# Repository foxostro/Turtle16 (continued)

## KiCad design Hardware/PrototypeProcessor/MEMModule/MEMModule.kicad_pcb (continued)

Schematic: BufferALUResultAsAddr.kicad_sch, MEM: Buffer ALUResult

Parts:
C6: 0.1μF; C_0603_1608Metric_Pad1.08x0.95mm_HandSolder
U5: 74AHCT16245; TSSOP-48_6.1x12.5mm_P0.5mm

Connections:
/MEM Prototype Inputs/Y_MEM0: U5.2 (1B1); also elsewhere on the board
/MEM Prototype Inputs/Y_MEM1: U5.3 (1B2); also elsewhere on the board
/MEM Prototype Inputs/Y_MEM2: U5.5 (1B3); also elsewhere on the board
/MEM Prototype Inputs/Y_MEM3: U5.6 (1B4); also elsewhere on the board
/MEM Prototype Inputs/Y_MEM4: U5.8 (1B5); also elsewhere on the board
/MEM Prototype Inputs/Y_MEM5: U5.9 (1B6); also elsewhere on the board
/MEM Prototype Inputs/Y_MEM6: U5.11 (1B7); also elsewhere on the board
/MEM Prototype Inputs/Y_MEM7: U5.12 (1B8); also elsewhere on the board
/MEM Prototype Inputs/Y_MEM8: U5.13 (2B1); also elsewhere on the board
/MEM Prototype Inputs/Y_MEM9: U5.14 (2B2); also elsewhere on the board
/MEM Prototype Inputs/Y_MEM10: U5.16 (2B3); also elsewhere on the board
/MEM Prototype Inputs/Y_MEM11: U5.17 (2B4); also elsewhere on the board
/MEM Prototype Inputs/Y_MEM12: U5.19 (2B5); also elsewhere on the board
/MEM Prototype Inputs/Y_MEM13: U5.20 (2B6); also elsewhere on the board
/MEM Prototype Inputs/Y_MEM14: U5.22 (2B7); also elsewhere on the board
/MEM Prototype Inputs/Y_MEM15: U5.23 (2B8); also elsewhere on the board
/MEM/~RDY: U5.25 (2~OE), U5.48 (1~OE); also elsewhere on the board
/Memory/Addr0: U5.47 (1A1); also elsewhere on the board
/Memory/Addr1: U5.46 (1A2); also elsewhere on the board
/Memory/Addr2: U5.44 (1A3); also elsewhere on the board
/Memory/Addr3: U5.43 (1A4); also elsewhere on the board
/Memory/Addr4: U5.41 (1A5); also elsewhere on the board
/Memory/Addr5: U5.40 (1A6); also elsewhere on the board
/Memory/Addr6: U5.38 (1A7); also elsewhere on the board
/Memory/Addr7: U5.37 (1A8); also elsewhere on the board
/Memory/Addr8: U5.36 (2A1); also elsewhere on the board
/Memory/Addr9: U5.35 (2A2); also elsewhere on the board
/Memory/Addr10: U5.33 (2A3); also elsewhere on the board
/Memory/Addr11: U5.32 (2A4); also elsewhere on the board
/Memory/Addr12: U5.30 (2A5); also elsewhere on the board
/Memory/Addr13: U5.29 (2A6); also elsewhere on the board
/Memory/Addr14: U5.27 (2A7); also elsewhere on the board
/Memory/Addr15: U5.26 (2A8); also elsewhere on the board
GND: C6.2, U5.1 (1DIR), U5.4 (GND), U5.10 (GND), U5.15 (GND), U5.21 (GND), U5.24 (2DIR), U5.28 (GND), U5.34 (GND), U5.39 (GND), U5.45 (GND); also elsewhere on the board
VCC: C6.1, U5.7 (VCC), U5.18 (VCC), U5.31 (VCC), U5.42 (VCC); also elsewhere on the board

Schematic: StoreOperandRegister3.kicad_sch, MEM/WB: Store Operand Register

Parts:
C8: 0.1μF; C_0603_1608Metric_Pad1.08x0.95mm_HandSolder
U7: 74ABT16374; TSSOP-48_6.1x12.5mm_P0.5mm

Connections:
/MEM Prototype Inputs/Phi1b: U7.25 (2CLK), U7.48 (1CLK); also elsewhere on the board
/MEM Prototype Outputs/StoreOp_WB0: U7.2 (1Q1); also elsewhere on the board
/MEM Prototype Outputs/StoreOp_WB1: U7.3 (1Q2); also elsewhere on the board
/MEM Prototype Outputs/StoreOp_WB2: U7.5 (1Q3); also elsewhere on the board
/MEM Prototype Outputs/StoreOp_WB3: U7.6 (1Q4); also elsewhere on the board
/MEM Prototype Outputs/StoreOp_WB4: U7.8 (1Q5); also elsewhere on the board
/MEM Prototype Outputs/StoreOp_WB5: U7.9 (1Q6); also elsewhere on the board
/MEM Prototype Outputs/StoreOp_WB6: U7.11 (1Q7); also elsewhere on the board
/MEM Prototype Outputs/StoreOp_WB7: U7.12 (1Q8); also elsewhere on the board
/MEM Prototype Outputs/StoreOp_WB8: U7.13 (2Q1); also elsewhere on the board
/MEM Prototype Outputs/StoreOp_WB9: U7.14 (2Q2); also elsewhere on the board
/MEM Prototype Outputs/StoreOp_WB10: U7.16 (2Q3); also elsewhere on the board
/MEM Prototype Outputs/StoreOp_WB11: U7.17 (2Q4); also elsewhere on the board
/MEM Prototype Outputs/StoreOp_WB12: U7.19 (2Q5); also elsewhere on the board
/MEM Prototype Outputs/StoreOp_WB13: U7.20 (2Q6); also elsewhere on the board
/MEM Prototype Outputs/StoreOp_WB14: U7.22 (2Q7); also elsewhere on the board
/MEM Prototype Outputs/StoreOp_WB15: U7.23 (2Q8); also elsewhere on the board
/Memory/IO0: U7.47 (1D1); also elsewhere on the board
/Memory/IO1: U7.46 (1D2); also elsewhere on the board
/Memory/IO2: U7.44 (1D3); also elsewhere on the board
/Memory/IO3: U7.43 (1D4); also elsewhere on the board
/Memory/IO4: U7.41 (1D5); also elsewhere on the board
/Memory/IO5: U7.40 (1D6); also elsewhere on the board
/Memory/IO6: U7.38 (1D7); also elsewhere on the board
/Memory/IO7: U7.37 (1D8); also elsewhere on the board
/Memory/IO8: U7.36 (2D1); also elsewhere on the board
/Memory/IO9: U7.35 (2D2); also elsewhere on the board
/Memory/IO10: U7.33 (2D3); also elsewhere on the board
/Memory/IO11: U7.32 (2D4); also elsewhere on the board
/Memory/IO12: U7.30 (2D5); also elsewhere on the board
/Memory/IO13: U7.29 (2D6); also elsewhere on the board
/Memory/IO14: U7.27 (2D7); also elsewhere on the board
/Memory/IO15: U7.26 (2D8); also elsewhere on the board
GND: C8.2, U7.1 (1~OE), U7.4 (GND), U7.10 (GND), U7.15 (GND), U7.21 (GND), U7.24 (2~OE), U7.28 (GND), U7.34 (GND), U7.39 (GND), U7.45 (GND); also elsewhere on the board
VCC: C8.1, U7.7 (VCC), U7.18 (VCC), U7.31 (VCC), U7.42 (VCC); also elsewhere on the board

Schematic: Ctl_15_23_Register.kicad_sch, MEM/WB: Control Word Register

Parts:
C7: 0.1μF; C_0603_1608Metric_Pad1.08x0.95mm_HandSolder
U6: 74ABT574; TSSOP-20_4.4x6.5mm_P0.65mm

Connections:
/MEM Prototype Inputs/Ctl_MEM17: U6.9 (D7); also elsewhere on the board
/MEM Prototype Inputs/Ctl_MEM18: U6.8 (D6); also elsewhere on the board
/MEM Prototype Inputs/Ctl_MEM19: U6.7 (D5); also elsewhere on the board
/MEM Prototype Inputs/Ctl_MEM20: U6.6 (D4); also elsewhere on the board
/MEM Prototype Inputs/Phi1b: U6.11 (Cp); also elsewhere on the board
/MEM Prototype Inputs/SelC_MEM0: U6.5 (D3); also elsewhere on the board
/MEM Prototype Inputs/SelC_MEM1: U6.4 (D2); also elsewhere on the board
/MEM Prototype Inputs/SelC_MEM2: U6.3 (D1); also elsewhere on the board
/MEM Prototype Outputs/Ctl_WB17: U6.12 (Q7); also elsewhere on the board
/MEM Prototype Outputs/Ctl_WB18: U6.13 (Q6); also elsewhere on the board
/MEM Prototype Outputs/Ctl_WB19: U6.14 (Q5); also elsewhere on the board
/MEM Prototype Outputs/Ctl_WB20: U6.15 (Q4); also elsewhere on the board
/MEM Prototype Outputs/SelC_WB0: U6.16 (Q3); also elsewhere on the board
/MEM Prototype Outputs/SelC_WB1: U6.17 (Q2); also elsewhere on the board
/MEM Prototype Outputs/SelC_WB2: U6.18 (Q1); also elsewhere on the board
GND: C7.2, U6.1 (OE), U6.10 (GND); also elsewhere on the board
VCC: C7.1, U6.2 (D0), U6.20 (VCC); also elsewhere on the board

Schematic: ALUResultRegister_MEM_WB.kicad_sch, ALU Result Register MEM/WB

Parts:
C11: 0.1μF; C_0603_1608Metric_Pad1.08x0.95mm_HandSolder
U8: 74ABT16374; TSSOP-48_6.1x12.5mm_P0.5mm

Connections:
/MEM Prototype Inputs/Phi1b: U8.25 (2CLK), U8.48 (1CLK); also elsewhere on the board
/MEM Prototype Inputs/Y_MEM0: U8.47 (1D1); also elsewhere on the board
/MEM Prototype Inputs/Y_MEM1: U8.46 (1D2); also elsewhere on the board
/MEM Prototype Inputs/Y_MEM2: U8.44 (1D3); also elsewhere on the board
/MEM Prototype Inputs/Y_MEM3: U8.43 (1D4); also elsewhere on the board
/MEM Prototype Inputs/Y_MEM4: U8.41 (1D5); also elsewhere on the board
/MEM Prototype Inputs/Y_MEM5: U8.40 (1D6); also elsewhere on the board
/MEM Prototype Inputs/Y_MEM6: U8.38 (1D7); also elsewhere on the board
/MEM Prototype Inputs/Y_MEM7: U8.37 (1D8); also elsewhere on the board
/MEM Prototype Inputs/Y_MEM8: U8.36 (2D1); also elsewhere on the board
/MEM Prototype Inputs/Y_MEM9: U8.35 (2D2); also elsewhere on the board
/MEM Prototype Inputs/Y_MEM10: U8.33 (2D3); also elsewhere on the board
/MEM Prototype Inputs/Y_MEM11: U8.32 (2D4); also elsewhere on the board
/MEM Prototype Inputs/Y_MEM12: U8.30 (2D5); also elsewhere on the board
/MEM Prototype Inputs/Y_MEM13: U8.29 (2D6); also elsewhere on the board
/MEM Prototype Inputs/Y_MEM14: U8.27 (2D7); also elsewhere on the board
/MEM Prototype Inputs/Y_MEM15: U8.26 (2D8); also elsewhere on the board
/MEM Prototype Outputs/Y_WB0: U8.2 (1Q1); also elsewhere on the board
/MEM Prototype Outputs/Y_WB1: U8.3 (1Q2); also elsewhere on the board
/MEM Prototype Outputs/Y_WB2: U8.5 (1Q3); also elsewhere on the board
/MEM Prototype Outputs/Y_WB3: U8.6 (1Q4); also elsewhere on the board
/MEM Prototype Outputs/Y_WB4: U8.8 (1Q5); also elsewhere on the board
/MEM Prototype Outputs/Y_WB5: U8.9 (1Q6); also elsewhere on the board
/MEM Prototype Outputs/Y_WB6: U8.11 (1Q7); also elsewhere on the board
/MEM Prototype Outputs/Y_WB7: U8.12 (1Q8); also elsewhere on the board
/MEM Prototype Outputs/Y_WB8: U8.13 (2Q1); also elsewhere on the board
/MEM Prototype Outputs/Y_WB9: U8.14 (2Q2); also elsewhere on the board
/MEM Prototype Outputs/Y_WB10: U8.16 (2Q3); also elsewhere on the board
/MEM Prototype Outputs/Y_WB11: U8.17 (2Q4); also elsewhere on the board
/MEM Prototype Outputs/Y_WB12: U8.19 (2Q5); also elsewhere on the board
/MEM Prototype Outputs/Y_WB13: U8.20 (2Q6); also elsewhere on the board
/MEM Prototype Outputs/Y_WB14: U8.22 (2Q7); also elsewhere on the board
/MEM Prototype Outputs/Y_WB15: U8.23 (2Q8); also elsewhere on the board
GND: C11.2, U8.1 (1~OE), U8.4 (GND), U8.10 (GND), U8.15 (GND), U8.21 (GND), U8.24 (2~OE), U8.28 (GND), U8.34 (GND), U8.39 (GND), U8.45 (GND); also elsewhere on the board
VCC: C11.1, U8.7 (VCC), U8.18 (VCC), U8.31 (VCC), U8.42 (VCC); also elsewhere on the board

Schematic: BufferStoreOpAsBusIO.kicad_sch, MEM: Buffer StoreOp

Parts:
C5: 0.1μF; C_0603_1608Metric_Pad1.08x0.95mm_HandSolder
TP41: ~{Assert}; TestPoint_Pad_D1.0mm
U4: 74AHCT16245; TSSOP-48_6.1x12.5mm_P0.5mm

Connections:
/MEM Prototype Inputs/StoreOp_MEM0: U4.23 (2B8); also elsewhere on the board
/MEM Prototype Inputs/StoreOp_MEM1: U4.22 (2B7); also elsewhere on the board
/MEM Prototype Inputs/StoreOp_MEM2: U4.20 (2B6); also elsewhere on the board
/MEM Prototype Inputs/StoreOp_MEM3: U4.19 (2B5); also elsewhere on the board
/MEM Prototype Inputs/StoreOp_MEM4: U4.17 (2B4); also elsewhere on the board
/MEM Prototype Inputs/StoreOp_MEM5: U4.16 (2B3); also elsewhere on the board
/MEM Prototype Inputs/StoreOp_MEM6: U4.14 (2B2); also elsewhere on the board
/MEM Prototype Inputs/StoreOp_MEM7: U4.13 (2B1); also elsewhere on the board
/MEM Prototype Inputs/StoreOp_MEM8: U4.12 (1B8); also elsewhere on the board
/MEM Prototype Inputs/StoreOp_MEM9: U4.11 (1B7); also elsewhere on the board
/MEM Prototype Inputs/StoreOp_MEM10: U4.9 (1B6); also elsewhere on the board
/MEM Prototype Inputs/StoreOp_MEM11: U4.8 (1B5); also elsewhere on the board
/MEM Prototype Inputs/StoreOp_MEM12: U4.6 (1B4); also elsewhere on the board
/MEM Prototype Inputs/StoreOp_MEM13: U4.5 (1B3); also elsewhere on the board
/MEM Prototype Inputs/StoreOp_MEM14: U4.3 (1B2); also elsewhere on the board
/MEM Prototype Inputs/StoreOp_MEM15: U4.2 (1B1); also elsewhere on the board
/MEM/Buffer StoreOp As Bus I/O/~Assert: TP41.1, U4.25 (2~OE), U4.48 (1~OE); also elsewhere on the board
/Memory/IO0: U4.26 (2A8); also elsewhere on the board
/Memory/IO1: U4.27 (2A7); also elsewhere on the board
/Memory/IO2: U4.29 (2A6); also elsewhere on the board
/Memory/IO3: U4.30 (2A5); also elsewhere on the board
/Memory/IO4: U4.32 (2A4); also elsewhere on the board
/Memory/IO5: U4.33 (2A3); also elsewhere on the board
/Memory/IO6: U4.35 (2A2); also elsewhere on the board
/Memory/IO7: U4.36 (2A1); also elsewhere on the board
/Memory/IO8: U4.37 (1A8); also elsewhere on the board
/Memory/IO9: U4.38 (1A7); also elsewhere on the board
/Memory/IO10: U4.40 (1A6); also elsewhere on the board
/Memory/IO11: U4.41 (1A5); also elsewhere on the board
/Memory/IO12: U4.43 (1A4); also elsewhere on the board
/Memory/IO13: U4.44 (1A3); also elsewhere on the board
/Memory/IO14: U4.46 (1A2); also elsewhere on the board
/Memory/IO15: U4.47 (1A1); also elsewhere on the board
GND: C5.2, U4.1 (1DIR), U4.4 (GND), U4.10 (GND), U4.15 (GND), U4.21 (GND), U4.24 (2DIR), U4.28 (GND), U4.34 (GND), U4.39 (GND), U4.45 (GND); also elsewhere on the board
VCC: C5.1, U4.7 (VCC), U4.18 (VCC), U4.31 (VCC), U4.42 (VCC); also elsewhere on the board

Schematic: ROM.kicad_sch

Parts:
C14, C15: 0.1μF; C_0603_1608Metric_Pad1.08x0.95mm_HandSolder
U11, U12: SST39SF010; 843221B1RKTP

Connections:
/MEM Prototype Inputs/FLUSH_IF: U11.22 (CE), U12.22 (CE); also elsewhere on the board
/Memory/Ins_IF0: U11.13 (D0); also elsewhere on the board
/Memory/Ins_IF1: U11.14 (D1); also elsewhere on the board
/Memory/Ins_IF2: U11.15 (D2); also elsewhere on the board
/Memory/Ins_IF3: U11.17 (D3); also elsewhere on the board
/Memory/Ins_IF4: U11.18 (D4); also elsewhere on the board
/Memory/Ins_IF5: U11.19 (D5); also elsewhere on the board
/Memory/Ins_IF6: U11.20 (D6); also elsewhere on the board
/Memory/Ins_IF7: U11.21 (D7); also elsewhere on the board
/Memory/Ins_IF8: U12.13 (D0); also elsewhere on the board
/Memory/Ins_IF9: U12.14 (D1); also elsewhere on the board
/Memory/Ins_IF10: U12.15 (D2); also elsewhere on the board
/Memory/Ins_IF11: U12.17 (D3); also elsewhere on the board
/Memory/Ins_IF12: U12.18 (D4); also elsewhere on the board
/Memory/Ins_IF13: U12.19 (D5); also elsewhere on the board
/Memory/Ins_IF14: U12.20 (D6); also elsewhere on the board
/Memory/Ins_IF15: U12.21 (D7); also elsewhere on the board
/Memory/PC0: U11.12 (A0), U12.12 (A0); also elsewhere on the board
/Memory/PC1: U11.11 (A1), U12.11 (A1); also elsewhere on the board
/Memory/PC2: U11.10 (A2), U12.10 (A2); also elsewhere on the board
/Memory/PC3: U11.9 (A3), U12.9 (A3); also elsewhere on the board
/Memory/PC4: U11.8 (A4), U12.8 (A4); also elsewhere on the board
/Memory/PC5: U11.7 (A5), U12.7 (A5); also elsewhere on the board
/Memory/PC6: U11.6 (A6), U12.6 (A6); also elsewhere on the board
/Memory/PC7: U11.5 (A7), U12.5 (A7); also elsewhere on the board
/Memory/PC8: U11.27 (A8), U12.27 (A8); also elsewhere on the board
/Memory/PC9: U11.26 (A9), U12.26 (A9); also elsewhere on the board
/Memory/PC10: U11.23 (A10), U12.23 (A10); also elsewhere on the board
/Memory/PC11: U11.25 (A11), U12.25 (A11); also elsewhere on the board
/Memory/PC12: U11.4 (A12), U12.4 (A12); also elsewhere on the board
/Memory/PC13: U11.28 (A13), U12.28 (A13); also elsewhere on the board
/Memory/PC14: U11.29 (A14), U12.29 (A14); also elsewhere on the board
/Memory/PC15: U11.3 (A15), U12.3 (A15); also elsewhere on the board
/Memory/RAMEN_R: U11.24 (OE), U12.24 (OE); also elsewhere on the board
GND: C14.2, C15.2, U11.2 (A16), U11.16 (GND), U12.2 (A16), U12.16 (GND); also elsewhere on the board
VCC: C14.1, C15.1, U11.31 (PGM), U11.32 (VCC), U12.31 (PGM), U12.32 (VCC); also elsewhere on the board

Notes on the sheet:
RAMEN_R enables the ROM. The right side of the RAM is used for Instruction Fetch. If the IF stage is not being fed by RAM then it is being fed by this ROM.

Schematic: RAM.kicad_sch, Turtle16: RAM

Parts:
C9, C10: 0.1μF; C_0603_1608Metric_Pad1.08x0.95mm_HandSolder
IC1: 7028L20PFGI; TQFP-100_14x14mm_P0.5mm; Manufacturer_Part_Number 7028L20PFGI; Mouser Part Number 972-7028L20PFGI

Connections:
/MEM Prototype Inputs/FLUSH_IF: IC1.59 (~OER); also elsewhere on the board
/Memory/Addr0: IC1.92 (A0L); also elsewhere on the board
/Memory/Addr1: IC1.93 (A1L); also elsewhere on the board
/Memory/Addr2: IC1.94 (A2L); also elsewhere on the board
/Memory/Addr3: IC1.95 (A3L); also elsewhere on the board
/Memory/Addr4: IC1.96 (A4L); also elsewhere on the board
/Memory/Addr5: IC1.97 (A5L); also elsewhere on the board
/Memory/Addr6: IC1.98 (A6L); also elsewhere on the board
/Memory/Addr7: IC1.99 (A7L); also elsewhere on the board
/Memory/Addr8: IC1.100 (A8L); also elsewhere on the board
/Memory/Addr9: IC1.1 (A9L); also elsewhere on the board
/Memory/Addr10: IC1.2 (A10L); also elsewhere on the board
/Memory/Addr11: IC1.3 (A11L); also elsewhere on the board
/Memory/Addr12: IC1.4 (A12L); also elsewhere on the board
/Memory/Addr13: IC1.5 (A13L); also elsewhere on the board
/Memory/Addr14: IC1.6 (A14L); also elsewhere on the board
/Memory/Addr15: IC1.7 (A15L); also elsewhere on the board
/Memory/IO0: IC1.37 (I/O0L); also elsewhere on the board
/Memory/IO1: IC1.36 (I/O1L); also elsewhere on the board
/Memory/IO2: IC1.34 (I/O2L); also elsewhere on the board
/Memory/IO3: IC1.33 (I/O3L); also elsewhere on the board
/Memory/IO4: IC1.32 (I/O4L); also elsewhere on the board
/Memory/IO5: IC1.31 (I/O5L); also elsewhere on the board
/Memory/IO6: IC1.30 (I/O6L); also elsewhere on the board
/Memory/IO7: IC1.29 (I/O7L); also elsewhere on the board
/Memory/IO8: IC1.27 (I/O8L); also elsewhere on the board
/Memory/IO9: IC1.26 (I/O9L); also elsewhere on the board
/Memory/IO10: IC1.25 (I/O10L); also elsewhere on the board
/Memory/IO11: IC1.24 (I/O11L); also elsewhere on the board
/Memory/IO12: IC1.23 (I/O12L); also elsewhere on the board
/Memory/IO13: IC1.22 (I/O13L); also elsewhere on the board
/Memory/IO14: IC1.21 (I/O14L); also elsewhere on the board
/Memory/IO15: IC1.20 (I/O15L); also elsewhere on the board
/Memory/Ins_IF0: IC1.39 (I/O0R); also elsewhere on the board
/Memory/Ins_IF1: IC1.40 (I/O1R); also elsewhere on the board
/Memory/Ins_IF2: IC1.41 (I/O2R); also elsewhere on the board
/Memory/Ins_IF3: IC1.42 (I/O3R); also elsewhere on the board
/Memory/Ins_IF4: IC1.43 (I/O4R); also elsewhere on the board
/Memory/Ins_IF5: IC1.44 (I/O5R); also elsewhere on the board
/Memory/Ins_IF6: IC1.45 (I/O6R); also elsewhere on the board
/Memory/Ins_IF7: IC1.47 (I/O7R); also elsewhere on the board
/Memory/Ins_IF8: IC1.48 (I/O8R); also elsewhere on the board
/Memory/Ins_IF9: IC1.49 (I/O9R); also elsewhere on the board
/Memory/Ins_IF10: IC1.51 (I/O10R); also elsewhere on the board
/Memory/Ins_IF11: IC1.52 (I/O11R); also elsewhere on the board
/Memory/Ins_IF12: IC1.53 (I/O12R); also elsewhere on the board
/Memory/Ins_IF13: IC1.54 (I/O13R); also elsewhere on the board
/Memory/Ins_IF14: IC1.55 (I/O14R); also elsewhere on the board
/Memory/Ins_IF15: IC1.56 (I/O15R); also elsewhere on the board
/Memory/PC0: IC1.84 (A0R); also elsewhere on the board
/Memory/PC1: IC1.83 (A1R); also elsewhere on the board
/Memory/PC2: IC1.82 (A2R); also elsewhere on the board
/Memory/PC3: IC1.81 (A3R); also elsewhere on the board
/Memory/PC4: IC1.80 (A4R); also elsewhere on the board
/Memory/PC5: IC1.79 (A5R); also elsewhere on the board
/Memory/PC6: IC1.78 (A6R); also elsewhere on the board
/Memory/PC7: IC1.77 (A7R); also elsewhere on the board
/Memory/PC8: IC1.76 (A8R); also elsewhere on the board
/Memory/PC9: IC1.75 (A9R); also elsewhere on the board
/Memory/PC10: IC1.74 (A10R); also elsewhere on the board
/Memory/PC11: IC1.73 (A11R); also elsewhere on the board
/Memory/PC12: IC1.72 (A12R); also elsewhere on the board
/Memory/PC13: IC1.71 (A13R); also elsewhere on the board
/Memory/PC14: IC1.70 (A14R); also elsewhere on the board
/Memory/PC15: IC1.69 (A15R); also elsewhere on the board
/Memory/RAMEN_L: IC1.13 (CE1L); also elsewhere on the board
/Memory/RAMEN_R: IC1.63 (CE1R); also elsewhere on the board
/Memory/~RAMEN_L: IC1.12 (~CE0L); also elsewhere on the board
/Memory/~RAMEN_R: IC1.64 (~CE0R); also elsewhere on the board
/System Bus Connector/~MemLoad: IC1.17 (~OEL); also elsewhere on the board
/System Bus Connector/~MemStore: IC1.16 (R/~WL); also elsewhere on the board
GND: C9.2, C10.2, IC1.10 (~LBL), IC1.11 (~UBL), IC1.18 (GND_1), IC1.19 (GND_2), IC1.35 (GND_3), IC1.38 (GND_4), IC1.57 (GND_5), IC1.58 (GND_6), IC1.61 (GND_7), IC1.65 (~UBR), IC1.66 (~LBR), IC1.87 (M/~S), IC1.88 (GND_8); also elsewhere on the board
VCC: C9.1, C10.1, IC1.14 (~SEML), IC1.15 (VCC_1), IC1.28 (VCC_2), IC1.46 (VCC_3), IC1.60 (R/~WR), IC1.62 (~SEMR), IC1.86 (~BUSYR), IC1.89 (~BUSYL); also elsewhere on the board

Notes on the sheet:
The RAM is configured in ~{S} mode to disable the onboard write arbitration logic.
If the IF stage is not being fed by ROM then it is being fed by RAM.

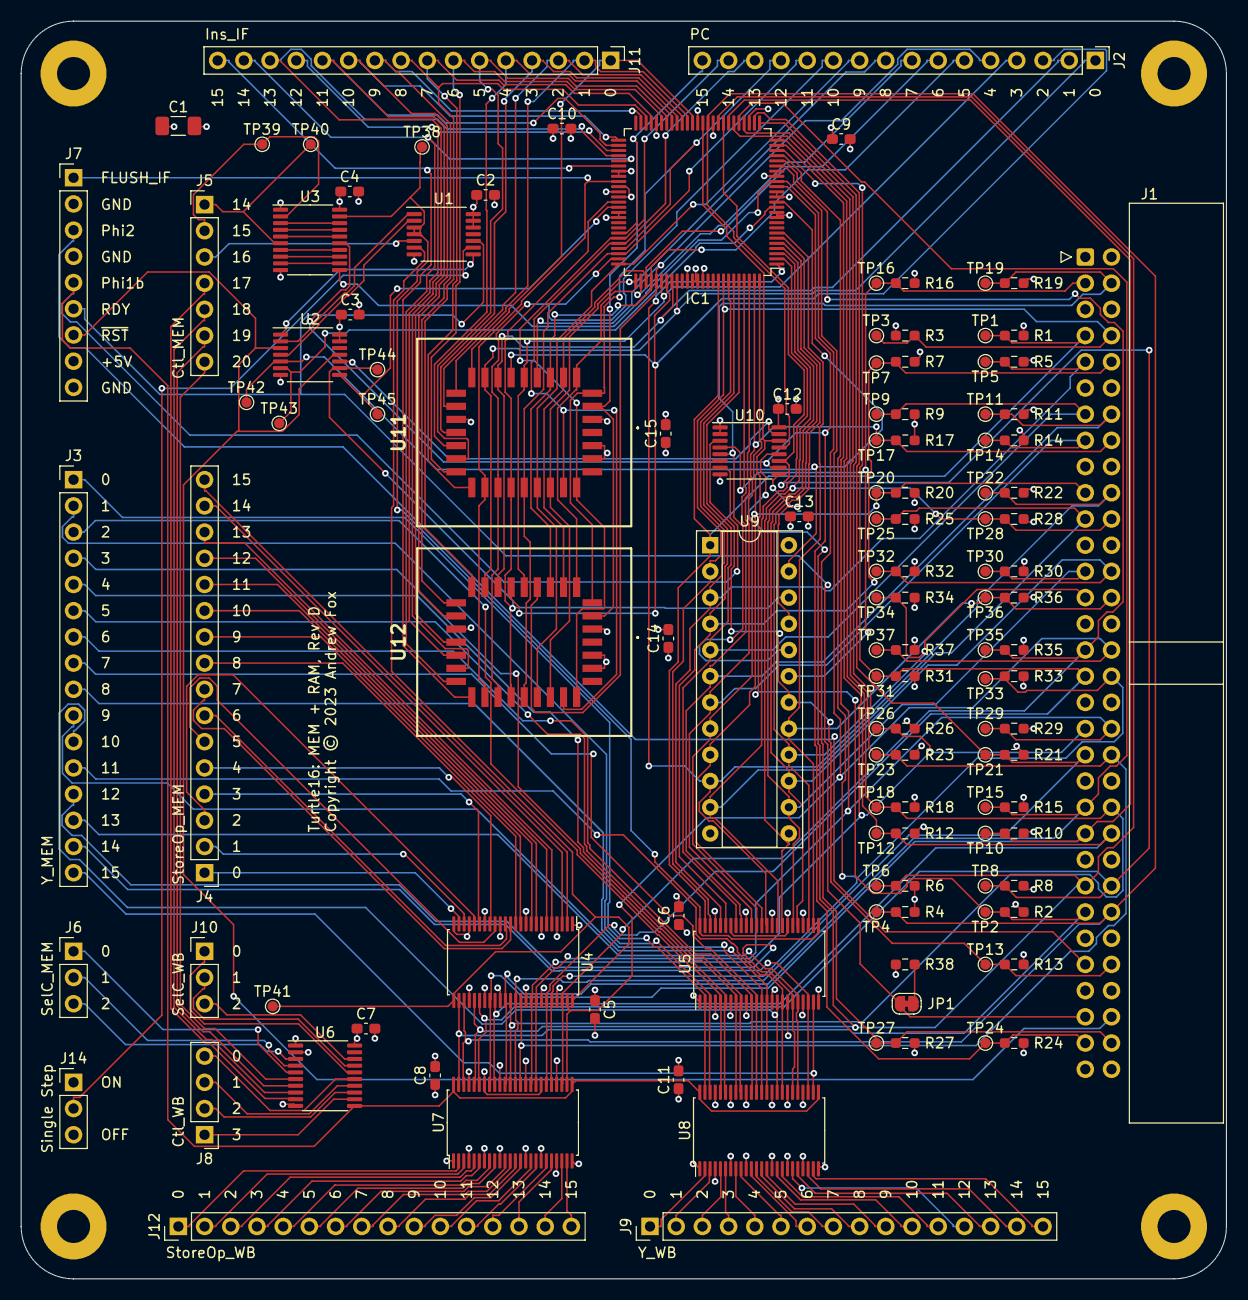
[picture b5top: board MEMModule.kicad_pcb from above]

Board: 4 copper layers, 116.8 x 121.9 mm, 129 parts (0 on the bottom side), 176 nets.

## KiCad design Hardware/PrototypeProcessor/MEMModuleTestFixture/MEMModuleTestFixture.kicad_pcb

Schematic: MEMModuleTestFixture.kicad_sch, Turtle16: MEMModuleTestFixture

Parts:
A1: Arduino_Nano_Every; Arduino_Nano
C1: 100µF; C_1206_3216Metric_Pad1.33x1.80mm_HandSolder
H1, H2, H3, H4: MountingHole_Pad; MountingHole_3.2mm_M3_Pad
J1: Power; 172448-0002

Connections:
/System Memory Bus Input/SCK: A1.24 (SCL/A5); also elsewhere on the board
/System Memory Bus Input/SO: A1.25 (A6); also elsewhere on the board
/System Memory Bus Input/~PL: A1.23 (SDA/A4); also elsewhere on the board
/System Memory Bus Output/RCLK: A1.21 (A2); also elsewhere on the board
/System Memory Bus Output/SCK: A1.20 (A1); also elsewhere on the board
/System Memory Bus Output/SI: A1.22 (A3); also elsewhere on the board
/System Memory Bus Output/~CLR: A1.19 (A0); also elsewhere on the board
/Test Fixture Inputs/SCK: A1.10 (D7); also elsewhere on the board
/Test Fixture Inputs/SO: A1.9 (D6); also elsewhere on the board
/Test Fixture Inputs/~PL: A1.11 (D8); also elsewhere on the board
/Test Fixture Outputs/RCLK: A1.6 (D3); also elsewhere on the board
/Test Fixture Outputs/SCK: A1.7 (D4); also elsewhere on the board
/Test Fixture Outputs/SI: A1.5 (D2); also elsewhere on the board
/Test Fixture Outputs/~CLR: A1.8 (D5); also elsewhere on the board
GND: A1.4 (GND), A1.29 (GND), C1.2, H1.1, H2.1, H3.1, H4.1, J1.2; also elsewhere on the board
VCC: A1.3 (~RESET), A1.28 (~RESET), A1.30 (VIN), C1.1, J1.1; also elsewhere on the board

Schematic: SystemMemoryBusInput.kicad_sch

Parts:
C26, C27, C28, C29, C30: 0.1µF; C_0603_1608Metric
U25, U26, U27, U28, U29: 74HC165; TSSOP-16_4.4x5mm_P0.65mm

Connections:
/System Bus Connector/Addr0: U27.11 (D0); also elsewhere on the board
/System Bus Connector/Addr1: U27.12 (D1); also elsewhere on the board
/System Bus Connector/Addr2: U27.13 (D2); also elsewhere on the board
/System Bus Connector/Addr3: U27.14 (D3); also elsewhere on the board
/System Bus Connector/Addr4: U27.3 (D4); also elsewhere on the board
/System Bus Connector/Addr5: U27.4 (D5); also elsewhere on the board
/System Bus Connector/Addr6: U27.5 (D6); also elsewhere on the board
/System Bus Connector/Addr7: U27.6 (D7); also elsewhere on the board
/System Bus Connector/Addr8: U28.11 (D0); also elsewhere on the board
/System Bus Connector/Addr9: U28.12 (D1); also elsewhere on the board
/System Bus Connector/Addr10: U28.13 (D2); also elsewhere on the board
/System Bus Connector/Addr11: U28.14 (D3); also elsewhere on the board
/System Bus Connector/Addr12: U28.3 (D4); also elsewhere on the board
/System Bus Connector/Addr13: U28.4 (D5); also elsewhere on the board
/System Bus Connector/Addr14: U28.5 (D6); also elsewhere on the board
/System Bus Connector/Addr15: U28.6 (D7); also elsewhere on the board
/System Bus Connector/Bank0: U29.11 (D0); also elsewhere on the board
/System Bus Connector/Bank1: U29.12 (D1); also elsewhere on the board
/System Bus Connector/Bank2: U29.13 (D2); also elsewhere on the board
/System Bus Connector/IO0: U25.11 (D0); also elsewhere on the board
/System Bus Connector/IO1: U25.12 (D1); also elsewhere on the board
/System Bus Connector/IO2: U25.13 (D2); also elsewhere on the board
/System Bus Connector/IO3: U25.14 (D3); also elsewhere on the board
/System Bus Connector/IO4: U25.3 (D4); also elsewhere on the board
/System Bus Connector/IO5: U25.4 (D5); also elsewhere on the board
/System Bus Connector/IO6: U25.5 (D6); also elsewhere on the board
/System Bus Connector/IO7: U25.6 (D7); also elsewhere on the board
/System Bus Connector/IO8: U26.11 (D0); also elsewhere on the board
/System Bus Connector/IO9: U26.12 (D1); also elsewhere on the board
/System Bus Connector/IO10: U26.13 (D2); also elsewhere on the board
/System Bus Connector/IO11: U26.14 (D3); also elsewhere on the board
/System Bus Connector/IO12: U26.3 (D4); also elsewhere on the board
/System Bus Connector/IO13: U26.4 (D5); also elsewhere on the board
/System Bus Connector/IO14: U26.5 (D6); also elsewhere on the board
/System Bus Connector/IO15: U26.6 (D7); also elsewhere on the board
/System Bus Connector/~MemLoad: U29.3 (D4); also elsewhere on the board
/System Bus Connector/~MemStore: U29.14 (D3); also elsewhere on the board
/System Memory Bus Input/SCK: U25.2 (CP), U26.2 (CP), U27.2 (CP), U28.2 (CP), U29.2 (CP); also elsewhere on the board
/System Memory Bus Input/SO: U29.9 (Q7); also elsewhere on the board
/System Memory Bus Input/~PL: U25.1 (~PL), U26.1 (~PL), U27.1 (~PL), U28.1 (~PL), U29.1 (~PL); also elsewhere on the board
GND: C26.2, C27.2, C28.2, C29.2, C30.2, U25.8 (GND), U25.10 (DS), U25.15 (~CE), U26.8 (GND), U26.15 (~CE), U27.8 (GND), U27.15 (~CE), U28.8 (GND), U28.15 (~CE), U29.4 (D5), U29.5 (D6), U29.6 (D7), U29.8 (GND), U29.15 (~CE); also elsewhere on the board
unnamed: U25.9 (Q7), U26.10 (DS)
unnamed: U26.9 (Q7), U27.10 (DS)
unnamed: U27.9 (Q7), U28.10 (DS)
unnamed: U28.9 (Q7), U29.10 (DS)
VCC: C26.1, C27.1, C28.1, C29.1, C30.1, U25.16 (VCC), U26.16 (VCC), U27.16 (VCC), U28.16 (VCC), U29.16 (VCC); also elsewhere on the board

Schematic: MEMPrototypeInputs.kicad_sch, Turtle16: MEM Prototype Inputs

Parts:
J8: PC; PinHeader_1x16_P2.54mm_Vertical
J9: Y_MEM; PinHeader_1x16_P2.54mm_Vertical
J10: StoreOp_MEM; PinHeader_1x16_P2.54mm_Vertical
J11: Ctl_MEM; PinHeader_1x07_P2.54mm_Vertical
J12: SelC_MEM; PinHeader_1x03_P2.54mm_Vertical
J13: Control Signals; PinHeader_1x09_P2.54mm_Vertical

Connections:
/Ctl_MEM14: J11.1; also elsewhere on the board
/Ctl_MEM15: J11.2; also elsewhere on the board
/Ctl_MEM16: J11.3; also elsewhere on the board
/Ctl_MEM17: J11.4; also elsewhere on the board
/Ctl_MEM18: J11.5; also elsewhere on the board
/Ctl_MEM19: J11.6; also elsewhere on the board
/Ctl_MEM20: J11.7; also elsewhere on the board
/MEM Prototype Inputs/FLUSH_IF: J13.1; also elsewhere on the board
/MEM Prototype Inputs/PC0: J8.1; also elsewhere on the board
/MEM Prototype Inputs/PC1: J8.2; also elsewhere on the board
/MEM Prototype Inputs/PC2: J8.3; also elsewhere on the board
/MEM Prototype Inputs/PC3: J8.4; also elsewhere on the board
/MEM Prototype Inputs/PC4: J8.5; also elsewhere on the board
/MEM Prototype Inputs/PC5: J8.6; also elsewhere on the board
/MEM Prototype Inputs/PC6: J8.7; also elsewhere on the board
/MEM Prototype Inputs/PC7: J8.8; also elsewhere on the board
/MEM Prototype Inputs/PC8: J8.9; also elsewhere on the board
/MEM Prototype Inputs/PC9: J8.10; also elsewhere on the board
/MEM Prototype Inputs/PC10: J8.11; also elsewhere on the board
/MEM Prototype Inputs/PC11: J8.12; also elsewhere on the board
/MEM Prototype Inputs/PC12: J8.13; also elsewhere on the board
/MEM Prototype Inputs/PC13: J8.14; also elsewhere on the board
/MEM Prototype Inputs/PC14: J8.15; also elsewhere on the board
/MEM Prototype Inputs/PC15: J8.16; also elsewhere on the board
/MEM Prototype Inputs/Phi1b: J13.5; also elsewhere on the board
/MEM Prototype Inputs/Phi2: J13.3; also elsewhere on the board
/MEM Prototype Inputs/RDY: J13.6; also elsewhere on the board
/MEM Prototype Inputs/~RST_sync: J13.7; also elsewhere on the board
/SelC_MEM0: J12.1; also elsewhere on the board
/SelC_MEM1: J12.2; also elsewhere on the board
/SelC_MEM2: J12.3; also elsewhere on the board
/StoreOp_MEM0: J10.1; also elsewhere on the board
/StoreOp_MEM1: J10.2; also elsewhere on the board
/StoreOp_MEM2: J10.3; also elsewhere on the board
/StoreOp_MEM3: J10.4; also elsewhere on the board
/StoreOp_MEM4: J10.5; also elsewhere on the board
/StoreOp_MEM5: J10.6; also elsewhere on the board
/StoreOp_MEM6: J10.7; also elsewhere on the board
/StoreOp_MEM7: J10.8; also elsewhere on the board
/StoreOp_MEM8: J10.9; also elsewhere on the board
/StoreOp_MEM9: J10.10; also elsewhere on the board
/StoreOp_MEM10: J10.11; also elsewhere on the board
/StoreOp_MEM11: J10.12; also elsewhere on the board
/StoreOp_MEM12: J10.13; also elsewhere on the board
/StoreOp_MEM13: J10.14; also elsewhere on the board
/StoreOp_MEM14: J10.15; also elsewhere on the board
/StoreOp_MEM15: J10.16; also elsewhere on the board
/Y_MEM0: J9.1; also elsewhere on the board
/Y_MEM1: J9.2; also elsewhere on the board
/Y_MEM2: J9.3; also elsewhere on the board
/Y_MEM3: J9.4; also elsewhere on the board
/Y_MEM4: J9.5; also elsewhere on the board
/Y_MEM5: J9.6; also elsewhere on the board
/Y_MEM6: J9.7; also elsewhere on the board
/Y_MEM7: J9.8; also elsewhere on the board
/Y_MEM8: J9.9; also elsewhere on the board
/Y_MEM9: J9.10; also elsewhere on the board
/Y_MEM10: J9.11; also elsewhere on the board
/Y_MEM11: J9.12; also elsewhere on the board
/Y_MEM12: J9.13; also elsewhere on the board
/Y_MEM13: J9.14; also elsewhere on the board
/Y_MEM14: J9.15; also elsewhere on the board
/Y_MEM15: J9.16; also elsewhere on the board
GND: J13.2, J13.4, J13.9; also elsewhere on the board
VCC: J13.8; also elsewhere on the board

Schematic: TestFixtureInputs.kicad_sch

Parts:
C2, C3, C4, C5, C6, C7, C8: 0.1µF; C_0603_1608Metric
U1, U2, U3, U4, U5, U6, U7: 74HC165; TSSOP-16_4.4x5mm_P0.65mm

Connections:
/Ctl_WB17: U7.11 (D0); also elsewhere on the board
/Ctl_WB18: U7.12 (D1); also elsewhere on the board
/Ctl_WB19: U7.13 (D2); also elsewhere on the board
/Ctl_WB20: U7.14 (D3); also elsewhere on the board
/Ins_IF0: U3.11 (D0); also elsewhere on the board
/Ins_IF1: U3.12 (D1); also elsewhere on the board
/Ins_IF2: U3.13 (D2); also elsewhere on the board
/Ins_IF3: U3.14 (D3); also elsewhere on the board
/Ins_IF4: U3.3 (D4); also elsewhere on the board
/Ins_IF5: U3.4 (D5); also elsewhere on the board
/Ins_IF6: U3.5 (D6); also elsewhere on the board
/Ins_IF7: U3.6 (D7); also elsewhere on the board
/Ins_IF8: U4.11 (D0); also elsewhere on the board
/Ins_IF9: U4.12 (D1); also elsewhere on the board
/Ins_IF10: U4.13 (D2); also elsewhere on the board
/Ins_IF11: U4.14 (D3); also elsewhere on the board
/Ins_IF12: U4.3 (D4); also elsewhere on the board
/Ins_IF13: U4.4 (D5); also elsewhere on the board
/Ins_IF14: U4.5 (D6); also elsewhere on the board
/Ins_IF15: U4.6 (D7); also elsewhere on the board
/SelC_WB0: U7.3 (D4); also elsewhere on the board
/SelC_WB1: U7.4 (D5); also elsewhere on the board
/SelC_WB2: U7.5 (D6); also elsewhere on the board
/StoreOp_WB0: U5.11 (D0); also elsewhere on the board
/StoreOp_WB1: U5.12 (D1); also elsewhere on the board
/StoreOp_WB2: U5.13 (D2); also elsewhere on the board
/StoreOp_WB3: U5.14 (D3); also elsewhere on the board
/StoreOp_WB4: U5.3 (D4); also elsewhere on the board
/StoreOp_WB5: U5.4 (D5); also elsewhere on the board
/StoreOp_WB6: U5.5 (D6); also elsewhere on the board
/StoreOp_WB7: U5.6 (D7); also elsewhere on the board
/StoreOp_WB8: U6.11 (D0); also elsewhere on the board
/StoreOp_WB9: U6.12 (D1); also elsewhere on the board
/StoreOp_WB10: U6.13 (D2); also elsewhere on the board
/StoreOp_WB11: U6.14 (D3); also elsewhere on the board
/StoreOp_WB12: U6.3 (D4); also elsewhere on the board
/StoreOp_WB13: U6.4 (D5); also elsewhere on the board
/StoreOp_WB14: U6.5 (D6); also elsewhere on the board
/StoreOp_WB15: U6.6 (D7); also elsewhere on the board
/Test Fixture Inputs/SCK: U1.2 (CP), U2.2 (CP), U3.2 (CP), U4.2 (CP), U5.2 (CP), U6.2 (CP), U7.2 (CP); also elsewhere on the board
/Test Fixture Inputs/SO: U7.9 (Q7); also elsewhere on the board
/Test Fixture Inputs/~PL: U1.1 (~PL), U2.1 (~PL), U3.1 (~PL), U4.1 (~PL), U5.1 (~PL), U6.1 (~PL), U7.1 (~PL); also elsewhere on the board
/Y_WB0: U1.11 (D0); also elsewhere on the board
/Y_WB1: U1.12 (D1); also elsewhere on the board
/Y_WB2: U1.13 (D2); also elsewhere on the board
/Y_WB3: U1.14 (D3); also elsewhere on the board
/Y_WB4: U1.3 (D4); also elsewhere on the board
/Y_WB5: U1.4 (D5); also elsewhere on the board
/Y_WB6: U1.5 (D6); also elsewhere on the board
/Y_WB7: U1.6 (D7); also elsewhere on the board
/Y_WB8: U2.11 (D0); also elsewhere on the board
/Y_WB9: U2.12 (D1); also elsewhere on the board
/Y_WB10: U2.13 (D2); also elsewhere on the board
/Y_WB11: U2.14 (D3); also elsewhere on the board
/Y_WB12: U2.3 (D4); also elsewhere on the board
/Y_WB13: U2.4 (D5); also elsewhere on the board
/Y_WB14: U2.5 (D6); also elsewhere on the board
/Y_WB15: U2.6 (D7); also elsewhere on the board
GND: C2.2, C3.2, C4.2, C5.2, C6.2, C7.2, C8.2, U1.8 (GND), U1.10 (DS), U1.15 (~CE), U2.8 (GND), U2.15 (~CE), U3.8 (GND), U3.15 (~CE), U4.8 (GND), U4.15 (~CE), U5.8 (GND), U5.15 (~CE), U6.8 (GND), U6.15 (~CE), U7.6 (D7), U7.8 (GND), U7.15 (~CE); also elsewhere on the board
unnamed: U1.9 (Q7), U2.10 (DS)
unnamed: U2.9 (Q7), U3.10 (DS)
unnamed: U3.9 (Q7), U4.10 (DS)
unnamed: U4.9 (Q7), U5.10 (DS)
unnamed: U5.9 (Q7), U6.10 (DS)
unnamed: U6.9 (Q7), U7.10 (DS)
VCC: C2.1, C3.1, C4.1, C5.1, C6.1, C7.1, C8.1, U1.16 (VCC), U2.16 (VCC), U3.16 (VCC), U4.16 (VCC), U5.16 (VCC), U6.16 (VCC), U7.16 (VCC); also elsewhere on the board
